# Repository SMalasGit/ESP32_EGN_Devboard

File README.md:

# ESP32_EGN_Devboard
A repository for an ESP32-S3 engineering development board I designed. It houses an ESP32, a buck-boost regulator, battery charging IC with power path, two BLDC motor drivers, a microSD-interface, and a camera.

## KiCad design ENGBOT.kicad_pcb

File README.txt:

This is a custom PCB for an ESP32 robot, meant to act as an educational tool for students and engineers alike. This PCB is built on 6 layers, features an ENIG finish, and uses Via-in-pad technology for compact size and function

This custom pcb has several unique features and can be combined with standard Arduino code libaries or off the shelf Epressif IDF IDE code to create a custom rover, robot, etc. This pcb features a custom lithium ion power path IC, allowing for power via USB-C, lithium ion battery, or both, depending on which power source is available. This IC also features battery protection and charging, allowing a user to know when the battery needs charging from the orange LED indicator, and when it is done charging from the green LED indicator

Furthermore, this pcb features a buck-boost regulator to allow a constant steady supply of 5 volts. In addition, this PCB includes a mosfet-based motor driver IC to control DC motors with ease. Since this board utilizes the powerful ESP32-S3 with a 240MHZ processor that includes Wifi, Bluetooth, and Zigbee, I have included a parallel camera interface connector, along with an SDIO microSD card connector. Finally, there is a series of GPIOs broken out for additional functionality, with UART and I2C capability.

Manufactured by JLCPCB standard 6 layer service.

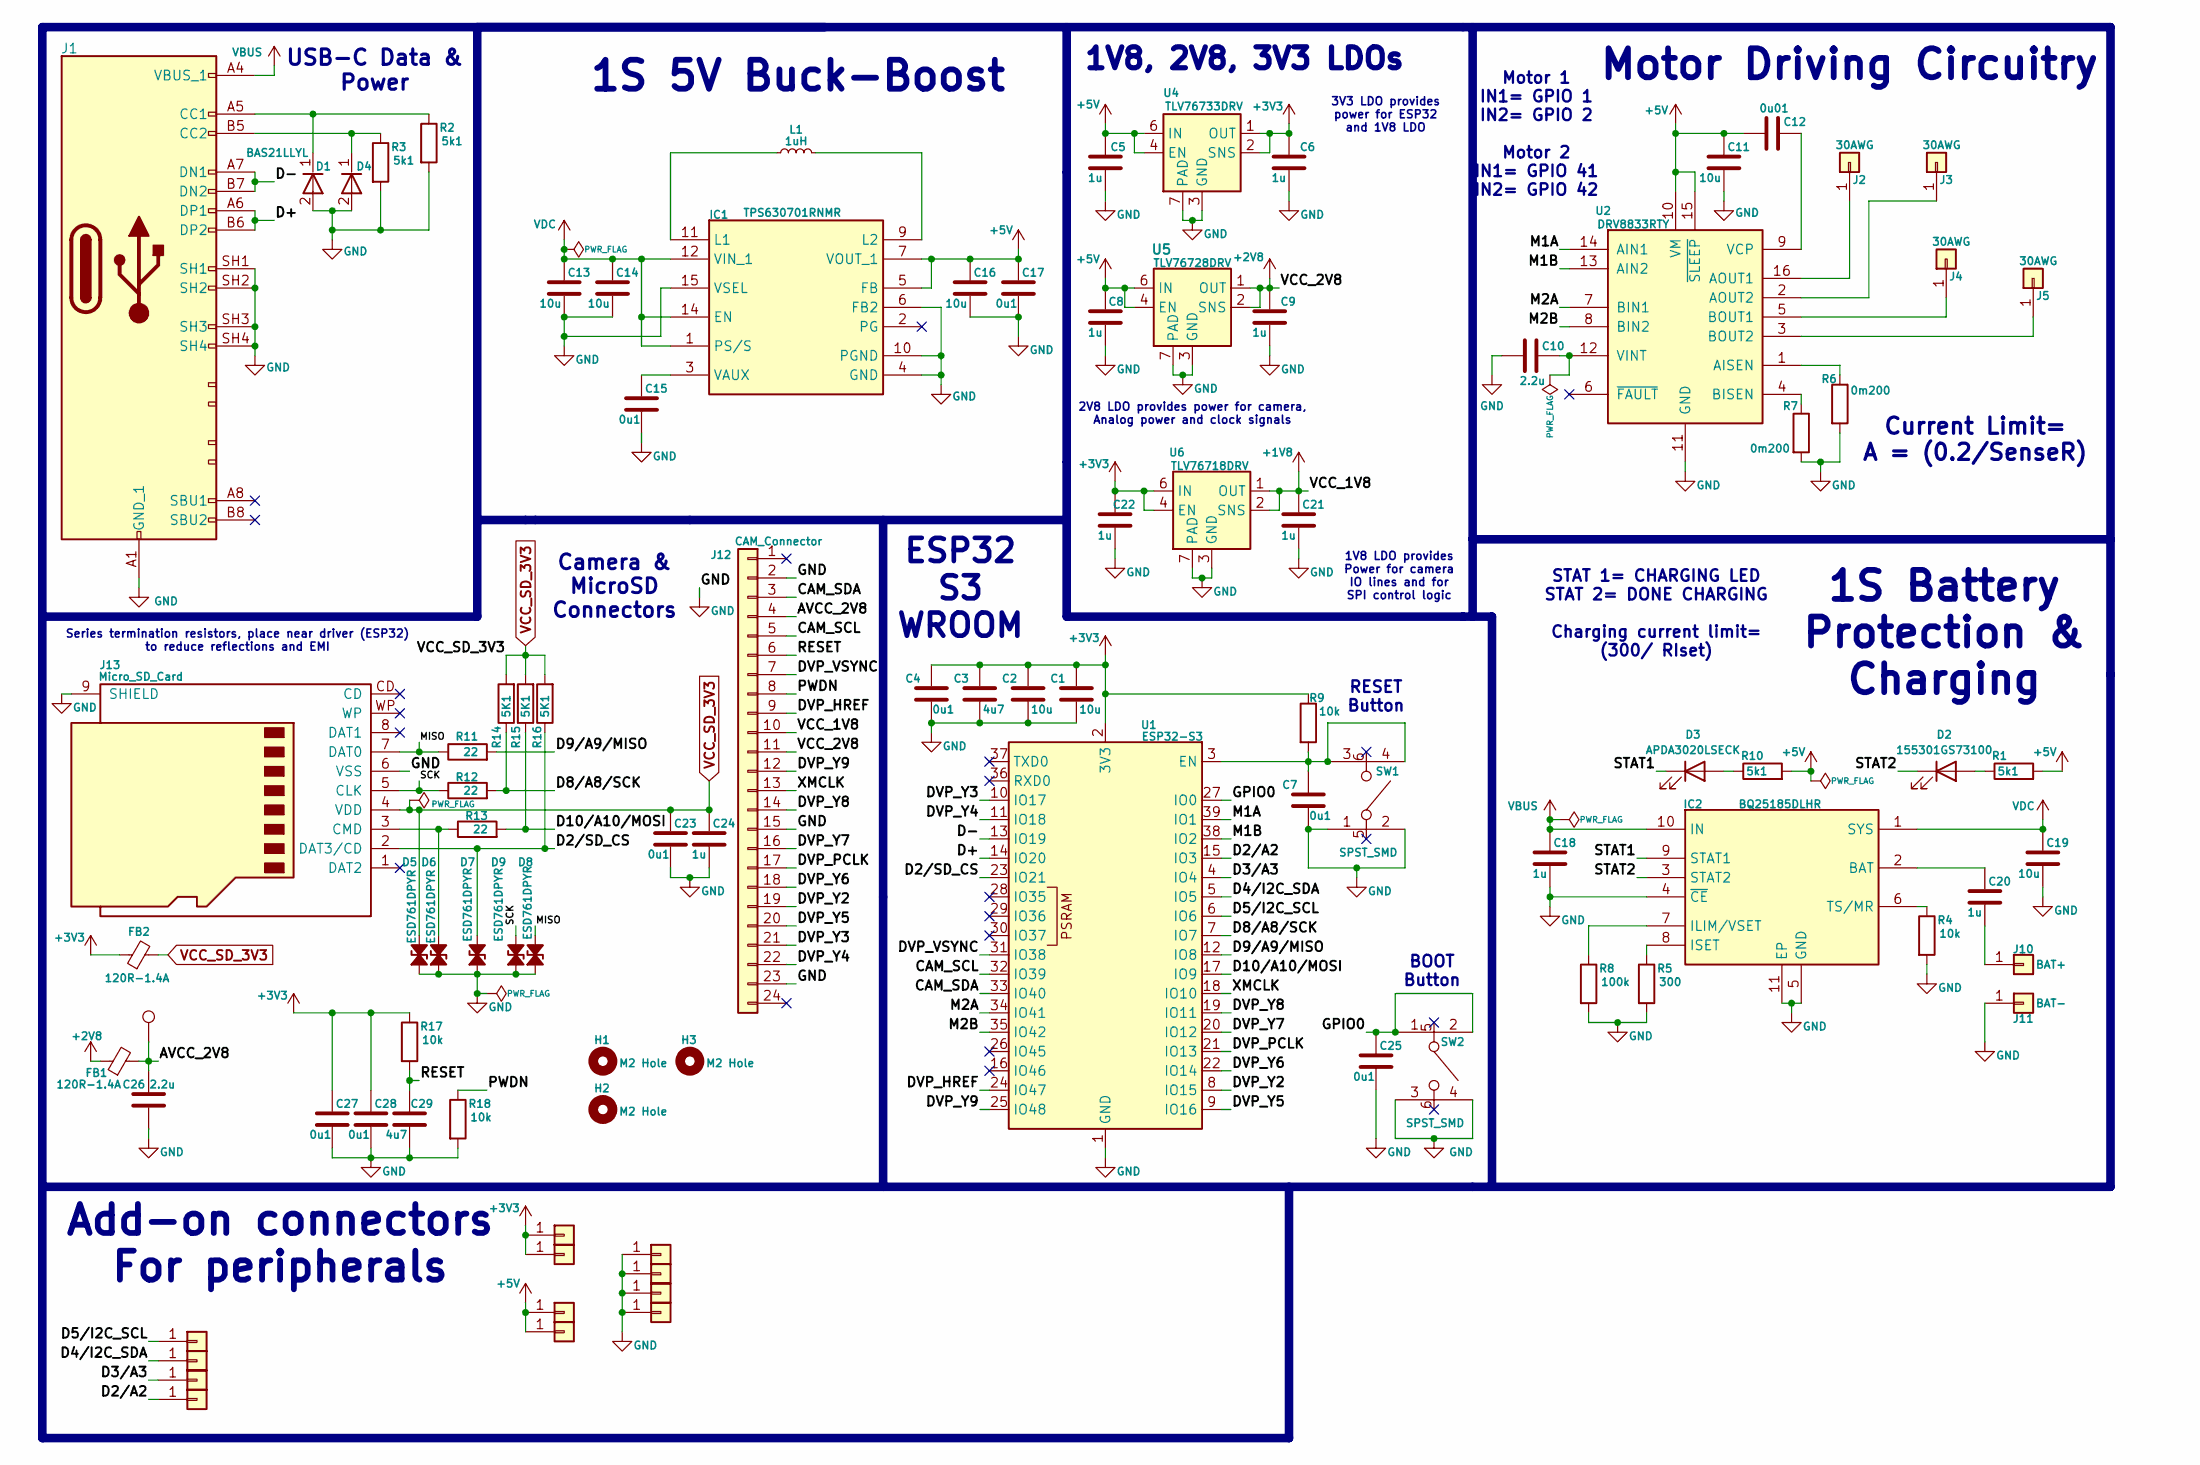
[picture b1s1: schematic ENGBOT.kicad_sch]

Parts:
C1, C2, C11, C13, C14, C16, C19: 10u; C_0402_1005Metric
C3, C29: 4u7; C_0402_1005Metric
C4, C7, C15, C17, C23, C25, C27, C28: 0u1; C_0402_1005Metric
C5, C6, C8, C9, C18, C20, C21, C22, C24: 1u; C_0603_1608Metric
C10, C26: 2.2u; C_0402_1005Metric
C12: 0u01; C_0402_1005Metric
D1, D4: BAS21LLYL; Mouser Part Number 771-BAS21LLYL
D2: 155301GS73100; 155301RS73100
D3: APDA3020LSECK; APDA3020LZGCK
D5, D6, D7, D8, D9: ESD761DPYR
FB1, FB2: 120R-1.4A; R_0603_1608Metric
H1, H2, H3: M2 Hole; MountingHole_2.2mm_M2_ISO7380
IC1: TPS630701RNMR; Mouser Part Number 595-TPS630701RNMR
IC2: BQ25185DLHR; SON40P220X200X80-11N; Mouser Part Number 595-BQ25185DLHR
J1: USB4215; GCT_USB4215-03-A_REVA
J2, J3, J4, J5: 30AWG; 30 AWG
J10: BAT+; BAT Wire
J11: BAT-; BAT Wire
J12: CAM_Connector; F33Z1A7Q1E8C24
J13: Micro_SD_Card; CUI_MSD-11-A
J14, J15, J16, J18, J19, J22, J23, J24, J25, J27, J28, J29: Conn_01x01; Motor Hole 30awg
L1: 1uH; INDC2520X120N
R1, R2, R3, R10: 5k1; R_0402_1005Metric
R4, R9, R17, R18: 10k; R_0402_1005Metric
R5: 300; R_0603_1608Metric
R6, R7: 0m200; C_0402_1005Metric
R8: 100k; R_1206_3216Metric
R11, R12, R13: 22; R_0402_1005Metric
R14, R15, R16: 5K1; R_0402_1005Metric
SW1, SW2: SPST_SMD; TS2134035BK160SMTTR
TP1: TestPoint; test
U1: ESP32-S3; ESP32-S3-WROOM-1
U2: DRV8833RTY; Texas_RTY_WQFN-16-1EP_4x4mm_P0.65mm_EP2.1x2.1mm_ThermalVias
U4: TLV76733DRV; WSON-6-1EP_2x2mm_P0.65mm_EP1x1.6mm_ThermalVias
U5: TLV76728DRV; WSON-6-1EP_2x2mm_P0.65mm_EP1x1.6mm_ThermalVias
U6: TLV76718DRV; WSON-6-1EP_2x2mm_P0.65mm_EP1x1.6mm_ThermalVias

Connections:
+1V8: C21.1, J12.10, U6.1 (OUT), U6.2 (SNS)
+2V8: C9.1, FB1.1, J12.11, U5.1 (OUT), U5.2 (SNS)
+3V3: C1.1, C2.1, C3.1, C4.1, C6.1, C22.1, C27.1, C28.1, FB2.1, J18.1, J19.1, R9.1, R17.1, U1.2 (3V3), U4.1 (OUT), U4.2 (SNS), U6.4 (EN), U6.6 (IN)
+5V: C5.1, C8.1, C11.1, C12.1, C16.1, C17.1, IC1.5 (FB), IC1.7 (VOUT_1), IC1.8 (VOUT_2), J24.1, J25.1, R1.2, R10.2, U2.10 (VM), U2.15 (~SLEEP), U4.4 (EN), U4.6 (IN), U5.4 (EN), U5.6 (IN)
/AVCC_2V8: C26.2, FB1.2, J12.4, TP1.1
/CAM_SCL: J12.5, U1.32 (IO39)
/CAM_SDA: J12.3, U1.33 (IO40)
/D2/A2: J14.1, U1.15 (IO3)
/D2/SD_CS: D7.2 (A2), J13.2 (DAT3/CD), R16.1, U1.23 (IO21)
/D3/A3: J29.1, U1.4 (IO4)
/D4/I2C_SDA: J28.1, U1.5 (IO5)
/D5/I2C_SCL: J27.1, U1.6 (IO6)
/D8/A8/SCK: R12.2, R14.1, U1.7 (IO7)
/D9/A9/MISO: R11.2, U1.12 (IO8)
/D10/A10/MOSI: R13.2, R15.1, U1.17 (IO9)
/D+: J1.A6 (DP1), J1.B6 (DP2), U1.14 (IO20)
/D-: J1.A7 (DN1), J1.B7 (DN2), U1.13 (IO19)
/DVP_HREF: J12.9, U1.24 (IO47)
/DVP_PCLK: J12.17, U1.21 (IO13)
/DVP_VSYNC: J12.7, U1.31 (IO38)
/DVP_Y2: J12.19, U1.8 (IO15)
/DVP_Y3: J12.21, U1.10 (IO17)
/DVP_Y4: J12.22, U1.11 (IO18)
/DVP_Y5: J12.20, U1.9 (IO16)
/DVP_Y6: J12.18, U1.22 (IO14)
/DVP_Y7: J12.16, U1.20 (IO12)
/DVP_Y8: J12.14, U1.19 (IO11)
/DVP_Y9: J12.12, U1.25 (IO48)
/GPIO0: C25.1, SW2.1 (A), SW2.2 (B), U1.27 (IO0)
/M1A: U1.39 (IO1), U2.14 (AIN1)
/M1B: U1.38 (IO2), U2.13 (AIN2)
/M2A: U1.34 (IO41), U2.7 (BIN1)
/M2B: U1.35 (IO42), U2.8 (BIN2)
/MISO: D8.2 (A2), J13.7 (DAT0), R11.1
/PWDN: J12.8, R18.1
/RESET: C29.1, J12.6, R17.2
/SCK: D9.2 (A2), J13.5 (CLK), R12.1
/STAT1: D3.1 (K), IC2.9 (STAT1)
/STAT2: D2.1 (K), IC2.3 (STAT2)
/XMCLK: J12.13, U1.18 (IO10)
GND: C1.2, C2.2, C3.2, C4.2, C5.2, C6.2, C7.2, C8.2, C9.2, C10.1, C11.2, C13.2, C14.2, C15.2, C16.2, C17.2, C18.2, C19.2, C21.2, C22.2, C23.2, C24.2, C25.2, C26.1, C27.2, C28.2, C29.2, D1.2 (A), D4.2 (A), D5.1 (A1), D6.1 (A1), D7.1 (A1), D8.1 (A1), D9.1 (A1), IC1.4 (GND), IC1.6 (FB2), IC1.10 (PGND), IC1.15 (VSEL), IC2.4 (~CE), IC2.5 (GND), IC2.11 (EP), J1.A1 (GND_1), J1.A12 (GND_2), J1.B1 (GND_3), J1.B12 (GND_4), J1.SH1, J1.SH2, J1.SH3, J1.SH4, J11.1, J12.2, J12.15, J12.23, J13.6 (VSS), J13.9 (SHIELD), J15.1, J16.1, J22.1, J23.1, R2.2, R3.2, R4.2, R5.2, R6.2, R7.2, R8.2, R18.2, SW1.1 (A), SW1.2 (B), SW2.3, SW2.4, U1.1 (GND), U1.40 (GND), U1.41 (GND), U2.11 (GND), U2.17 (GND), U4.3 (GND), U4.5 (GND), U4.7 (PAD), U5.3 (GND), U5.5 (GND), U5.7 (PAD), U6.3 (GND), U6.5 (GND), U6.7 (PAD)
unnamed: D1.1 (K), J1.A5 (CC1), R2.1
unnamed: D2.2 (A), R1.1
unnamed: D3.2 (A), R10.1
unnamed: D4.1 (K), J1.B5 (CC2), R3.1
unnamed: D6.2 (A2), J13.3 (CMD), R13.1
unnamed: IC1.11 (L1), L1.1
unnamed: IC1.9 (L2), L1.2
unnamed: C15.1, IC1.3 (VAUX)
unnamed: C20.1, IC2.2 (BAT)
unnamed: IC2.7 (ILIM/VSET), R8.1
unnamed: IC2.8 (ISET), R5.1
unnamed: IC2.6 (TS/MR), R4.1
unnamed: J2.1, U2.16 (AOUT1)
unnamed: J3.1, U2.2 (AOUT2)
unnamed: J4.1, U2.5 (BOUT1)
unnamed: J5.1, U2.3 (BOUT2)
unnamed: C20.2, J10.1
unnamed: C7.1, R9.2, SW1.3, SW1.4, U1.3 (EN)
unnamed: R6.1, U2.1 (AISEN)
unnamed: R7.1, U2.4 (BISEN)
unnamed: C12.2, U2.9 (VCP)
unnamed: C10.2, U2.12 (VINT)
VBUS: C18.1, IC2.10 (IN), J1.A4 (VBUS_1), J1.A9 (VBUS_2), J1.B4 (VBUS_3), J1.B9 (VBUS_4)
VCC_SD_3V3: C23.1, C24.1, D5.2 (A2), FB2.2, J13.4 (VDD), R14.2, R15.2, R16.2
VDC: C13.1, C14.1, C19.1, IC1.1 (PS/S), IC1.12 (VIN_1), IC1.13 (VIN_2), IC1.14 (EN), IC2.1 (SYS)

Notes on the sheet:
Motor 1 IN1= GPIO 1 IN2= GPIO 2 Motor 2 IN1= GPIO 41 IN2= GPIO 42
ESP32 S3 WROOM
1S Battery Protection & Charging
STAT 1= CHARGING LED STAT 2= DONE CHARGING Charging current limit= (300/ RIset)
2V8 LDO provides power for camera, Analog power and clock signals
Camera & MicroSD Connectors
RESET Button
1S 5V Buck-Boost
1V8 LDO provides Power for camera IO lines and for SPI control logic
Motor Driving Circuitry
USB-C Data & Power
BOOT Button
Add-on connectors For peripherals
1V8, 2V8, 3V3 LDOs
3V3 LDO provides power for ESP32 and 1V8 LDO
Current Limit= A = (0.2/SenseR)
Series termination resistors, place near driver (ESP32) to reduce reflections and EMI

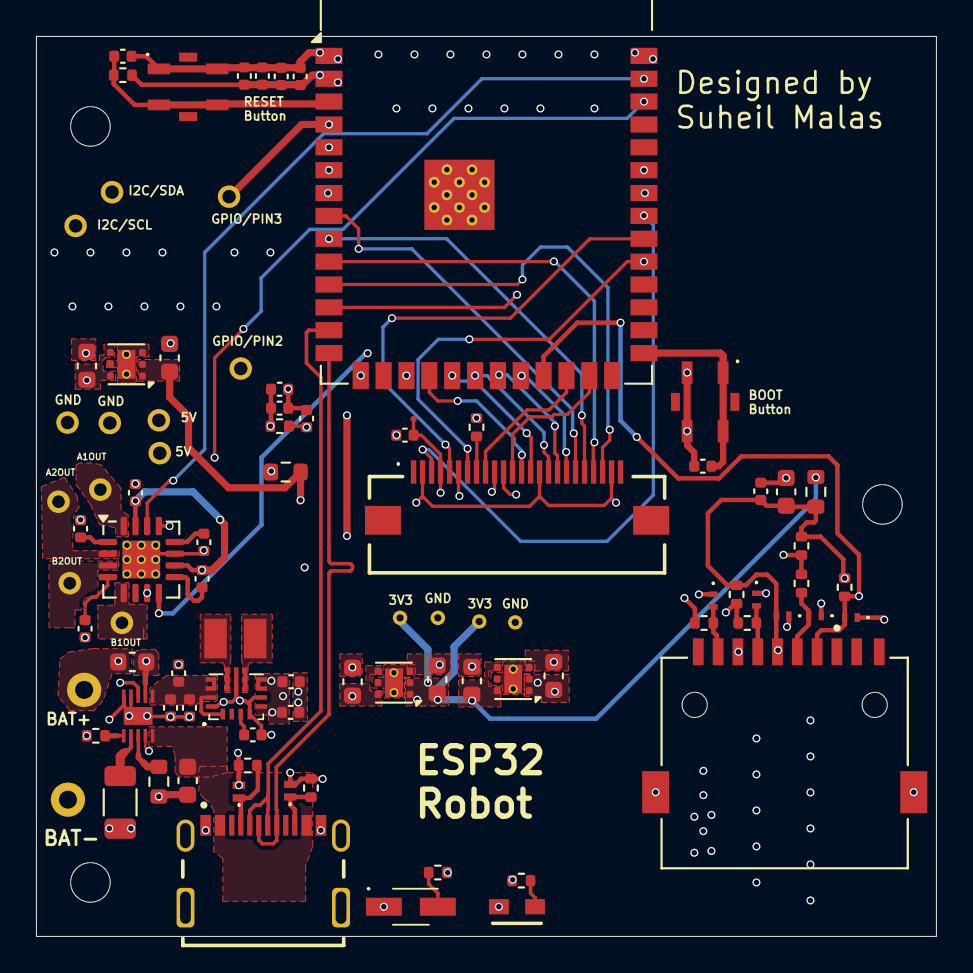
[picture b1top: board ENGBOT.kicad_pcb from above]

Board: 6 copper layers, 50.0 x 50.0 mm, 93 parts (0 on the bottom side), 66 nets.
